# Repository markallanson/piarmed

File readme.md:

Piarmed
=======

Alarm System powered by Raspberry Pi and Node.js.

Install
-------
    cd src
    npm install

Configure
---------
### Enable I2C
### Grant executing user correct privs
The user running piarmed needs the right priviliges to do so.

    sudo adduser <user> i2c
    sudo adduser <user> gpio

### Wire everything up

Run
---
    cd svr
    npm piarmed.js | bunyan

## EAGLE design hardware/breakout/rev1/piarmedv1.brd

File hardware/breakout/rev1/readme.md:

This directory contains the eagle schematic and board files for the rev 1
piarmed breakout board.

The rev 1 board contains support for 9 zones, which allows the board to
be the same width as the Raspberry Pi Zero.

# Eagle Parts

## Custom parts
There are 2 custom parts in the piarmed.lbr file in this directory.

### 3x18 Header
I use this with a 3x18 right angle connector from ebay. Actually there is no
such thing, I just got some 3x40 right angle connectors and snipped down to
3x18.

[Sourced from ebay, here] [1].

### Transformer
This is a part to accommodate the placement of a simple small 12v-5v buck
converter.

[Sourced from ebay, here] [2].

## Other parts
The raspberry pi connector is from the [SparkFun Connectors library] [3].

# Inventory
Here's what you will need to assemble the breakout board.

   * 1 - 2x20 2.54mm female header.
   * 1 - 2x20 2.54mm male header.
   * 1 - 3x18 right angle header (doesn't need to be right angle, but this is the way I am assembling it)
   * 1 - [Ebay buck converter] [2].
   * 1 - DC power jack with positive tip polarity.
   * 4 - 3mm LEDS of your favourite colours.
   * 4 - 220ohm resistors. [I used a TE Connectivity resistor - Farnell part 2329900] [4]
   * 18 - 22kohm resistors. [I used a TE Connectivity resistor - Farnell part 2329901] [5]
   * 1 - 1x2 male header (power to Raspberry Pi)
   * 1 - 1x2 female header (to build power cable for the Raspberry Pi)
   * 1 - Micro USB connector

Misc bits
   * Short wires to build power cable
   * Some heat shrink to build power cable.

# Manufacturing
I used [Elecrow] [6] to manufacture the boards. They supply the CAM files and also DRC files
to be used in eagle.

# Known Issues
Rev 1 board has one known issue - the power header to supply the Raspberry Pi is too close to
the Micro USB power port on the Raspberry Pi, so you need to bend your header back towards
the DC power jack in order to make your power cable fit.

[1]: http://www.ebay.co.uk/itm/161947559638
[2]: http://www.ebay.co.uk/itm/171464543948
[3]: https://github.com/sparkfun/SparkFun-Eagle-Libraries
[4]: http://uk.farnell.com/te-connectivity/lr0204f220r/resistor-metal-220r-0-25w-1/dp/2329900
[5]: http://uk.farnell.com/te-connectivity/lr0204f220r/resistor-metal-220r-0-25w-1/dp/2329901
[6]: http://www.elecrow.com/10pcs-2-layer-pcb-p-1175.html

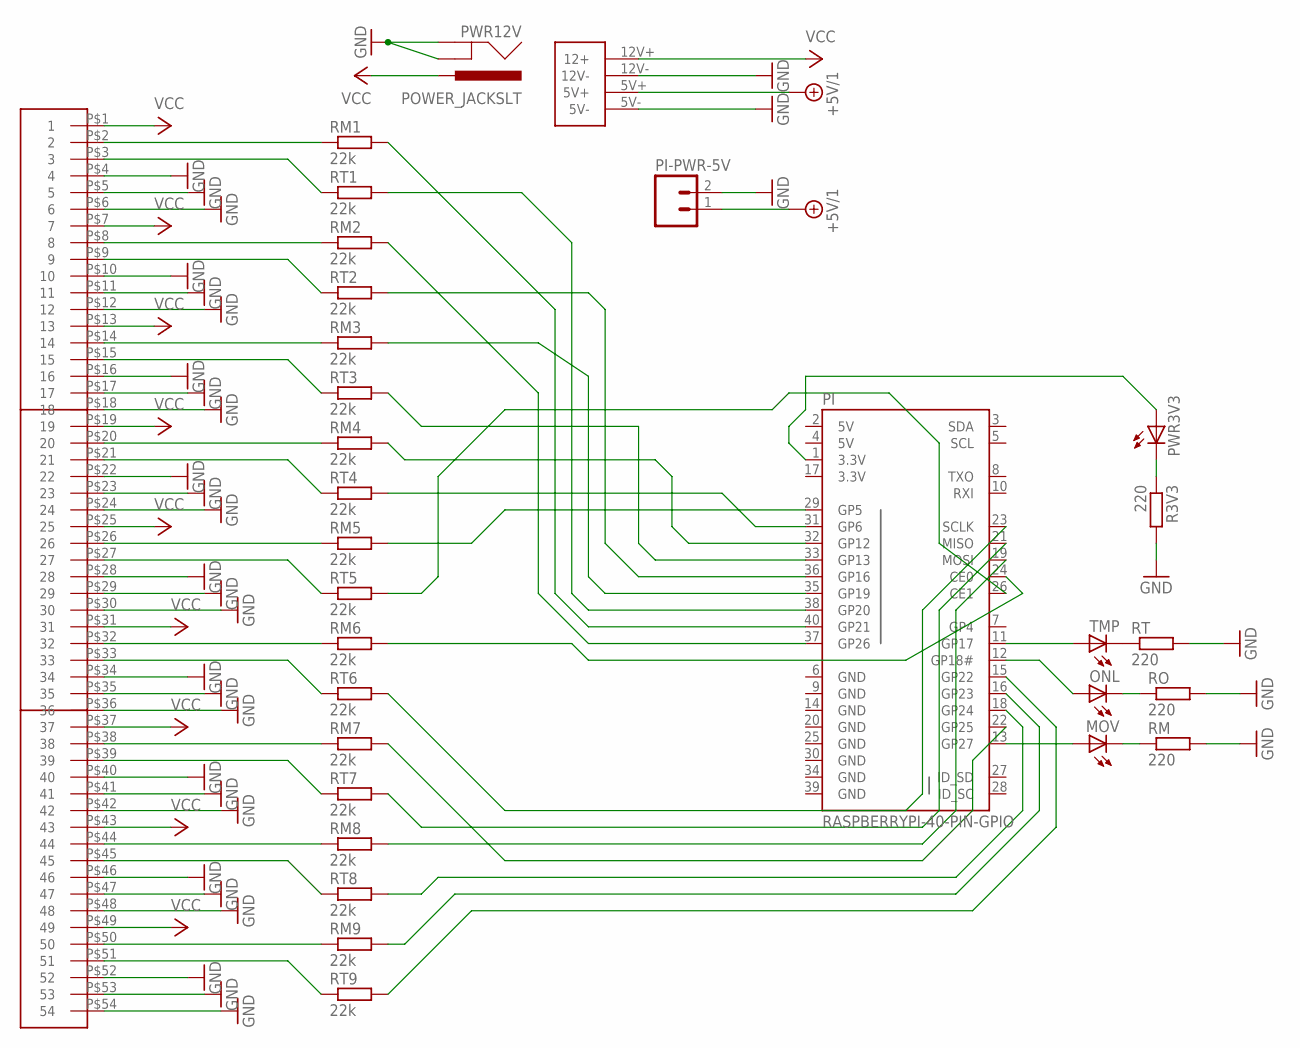
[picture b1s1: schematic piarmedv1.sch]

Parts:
MOV: LED3MM
ONL: LED3MM
PI: RASPBERRYPI-40-PIN-GPIO; 2X20-SHROUDED
PI-PWR-5V: M02PTH; 1X02
PWR3V3: LED3MM
PWR12V: POWER_JACKSLT; POWER_JACK_SLOT
R3V3: 220; 0204/5
RM: 220; 0204/5
RM1, RM2, RM3, RM4, RM5, RM6, RM7, RM8, RM9: 22k; 0204/5
RO: 220; 0204/5
RT: 220; 0204/5
RT1, RT2, RT3, RT4, RT5, RT6, RT7, RT8, RT9: 22k; 0204/5
TMP: LED3MM
U$1: POWER-12V-5VSTD; 4PIN
U$2: 3X18HEADER

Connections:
3.3V: PI.17 (3.3V)
5V: PI.2 (5V), PI.4 (5V)
+5V/1: PI-PWR-5V.1, U$1.5V+
GND: PI.6 (GND), PI.9 (GND), PI.14 (GND), PI.20 (GND), PI.25 (GND), PI.30 (GND), PI.34 (GND), PI.39 (GND), PI-PWR-5V.2, PWR12V.GND@1 (GNDBREAK), PWR12V.GND@2 (GND), R3V3.2, RM.2, RO.2, RT.2, U$1.5V-, U$1.12V-, U$2.P$4 (4), U$2.P$5 (5), U$2.P$6 (6), U$2.P$10 (10), U$2.P$11 (11), U$2.P$12 (12), U$2.P$16 (16), U$2.P$17 (17), U$2.P$18 (18), U$2.P$22 (22), U$2.P$23 (23), U$2.P$24 (24), U$2.P$28 (28), U$2.P$29 (29), U$2.P$30 (30), U$2.P$34 (34), U$2.P$35 (35), U$2.P$36 (36), U$2.P$40 (40), U$2.P$41 (41), U$2.P$42 (42), U$2.P$46 (46), U$2.P$47 (47), U$2.P$48 (48), U$2.P$52 (52), U$2.P$53 (53), U$2.P$54 (54)
unnamed: PWR3V3.K (C), R3V3.1
unnamed: ONL.K (C), RO.1
unnamed: RT.1, TMP.K (C)
unnamed: MOV.K (C), RM.1
unnamed: ONL.A, PI.12 (GP18#)
unnamed: PI.11 (GP17), TMP.A
unnamed: MOV.A, PI.13 (GP27)
unnamed: PI.40 (GP21), RM1.2
unnamed: PI.38 (GP20), RT1.2
unnamed: PI.37 (GP26), RM2.2
unnamed: PI.36 (GP16), RT2.2
unnamed: PI.35 (GP19), RM3.2
unnamed: PI.33 (GP13), RT3.2
unnamed: PI.32 (GP12), RM4.2
unnamed: PI.31 (GP6), RT4.2
unnamed: PI.29 (GP5), RM5.2
unnamed: PI.26 (CE1), RT5.2
unnamed: PI.24 (CE0), RM6.2
unnamed: PI.23 (SCLK), RT6.2
unnamed: RM1.1, U$2.P$2 (2)
unnamed: PI.21 (MISO), RT7.2
unnamed: PI.19 (MOSI), RM8.2
unnamed: PI.18 (GP24), RT8.2
unnamed: PI.16 (GP23), RM9.2
unnamed: PI.15 (GP22), RT9.2
unnamed: RT1.1, U$2.P$3 (3)
unnamed: RM2.1, U$2.P$8 (8)
unnamed: RT2.1, U$2.P$9 (9)
unnamed: RM3.1, U$2.P$14 (14)
unnamed: RT3.1, U$2.P$15 (15)
unnamed: RM4.1, U$2.P$20 (20)
unnamed: RT4.1, U$2.P$21 (21)
unnamed: PI.22 (GP25), RM7.2
unnamed: RM5.1, U$2.P$26 (26)
unnamed: RT5.1, U$2.P$27 (27)
unnamed: RM6.1, U$2.P$32 (32)
unnamed: RT6.1, U$2.P$33 (33)
unnamed: RM7.1, U$2.P$38 (38)
unnamed: RT7.1, U$2.P$39 (39)
unnamed: RM8.1, U$2.P$44 (44)
unnamed: RT8.1, U$2.P$45 (45)
unnamed: RM9.1, U$2.P$50 (50)
unnamed: RT9.1, U$2.P$51 (51)
POWER: PI.1 (3.3V), PWR3V3.A
VCC: PWR12V.PWR, U$1.12V+ (12+), U$2.P$1 (1), U$2.P$7 (7), U$2.P$13 (13), U$2.P$19 (19), U$2.P$25 (25), U$2.P$31 (31), U$2.P$37 (37), U$2.P$43 (43), U$2.P$49 (49)

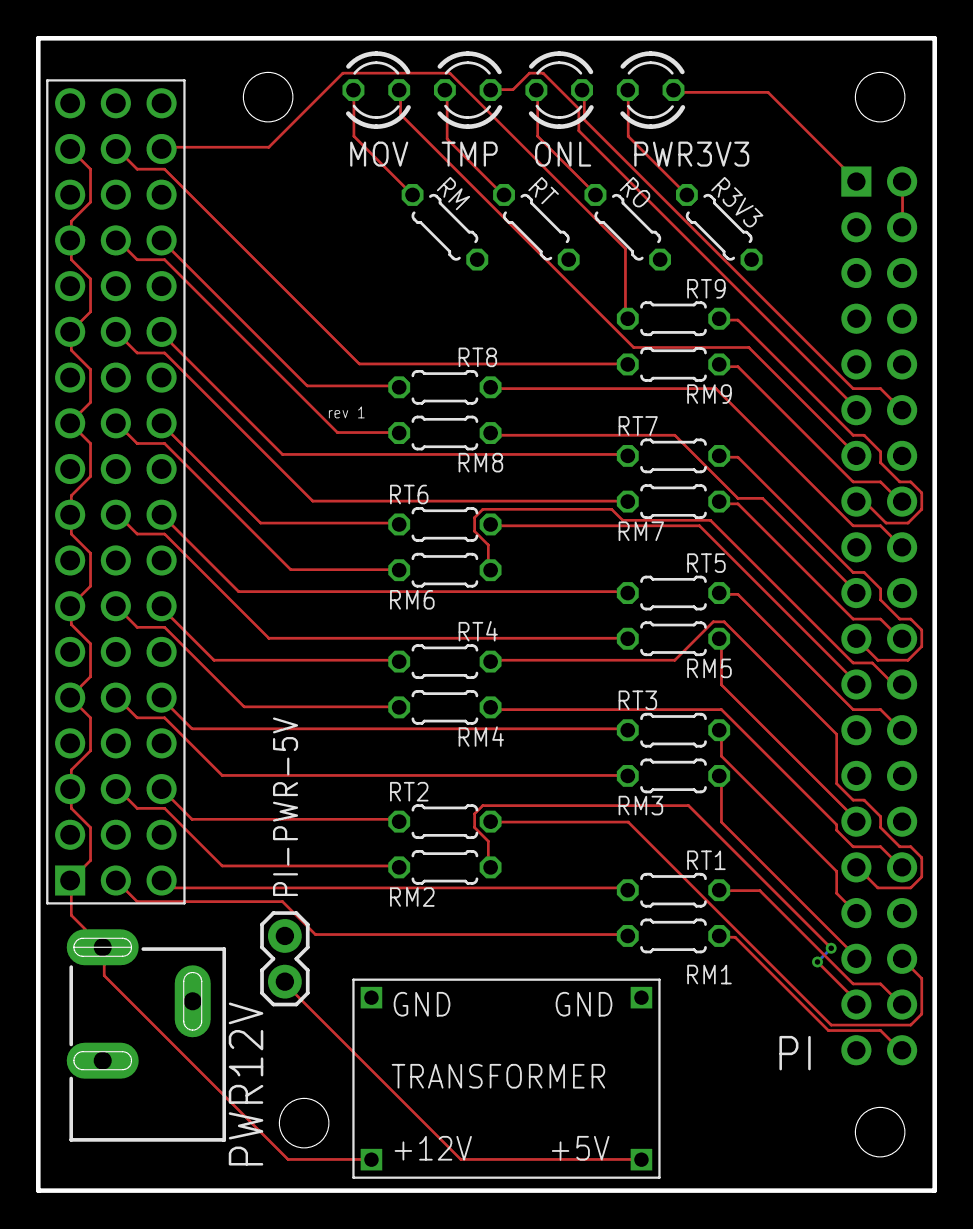
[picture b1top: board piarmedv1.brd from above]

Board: 2 copper layers, 49.8 x 64.0 mm, 32 parts (0 on the bottom side), 48 nets.

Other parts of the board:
U$3: 719DPILOGO

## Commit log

2016-01-03 Initial Commit - Basic Tamper support for a single PIR
2016-01-04 Abstracted GPIO reading away from the generator itself and into a Data adaptor. Adding this abstraction layer is going to be important when the mux code is added later.
2016-01-04 Add an explicit start and stop for the adaptors so we can add support for an initial read. Fixed NC/NO switch information in tamper processing, and rationalized tamper configuration.
2016-01-06 Add movement sensing to GenericPIR
2016-01-06 Updated device overlay to add gpio 25
2016-01-09 Added MCP23017 IC support as a source of data. Added software filter between the signal and the PIR in order to do simple noise filtering. GenericPIR now remembers its state and will only broadcast m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
2016-01-24 Now config driven. Added LED Notifiers and outbound data adaption framework. Added bunyan logging. added combos concept and 1 slackbot interface combo.
2016-02-20 Now reacts to presence alerts received via the slack channel to arm and disarm the alarm. Will send notifications to slack if movement is detected while the alarm is armed. Disarming the alarm during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
2016-04-25 Start service, added switch generator.
2016-05-07 Removed ICs from the circuit as modern Pi's have enough GPIO pins to handle my use case.
2016-07-16 Added eagle files for the schematic and board layout for the piarmed breakout board, and a readme to explain some of the details.
2016-07-16 Fixed some markdown syntax issues.

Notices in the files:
parts and their libraries:
SparkFun-Boards: Licensing: Creative Commons ShareAlike 4.0 International - https://creativecommons.org/licenses/by-sa/4.0
